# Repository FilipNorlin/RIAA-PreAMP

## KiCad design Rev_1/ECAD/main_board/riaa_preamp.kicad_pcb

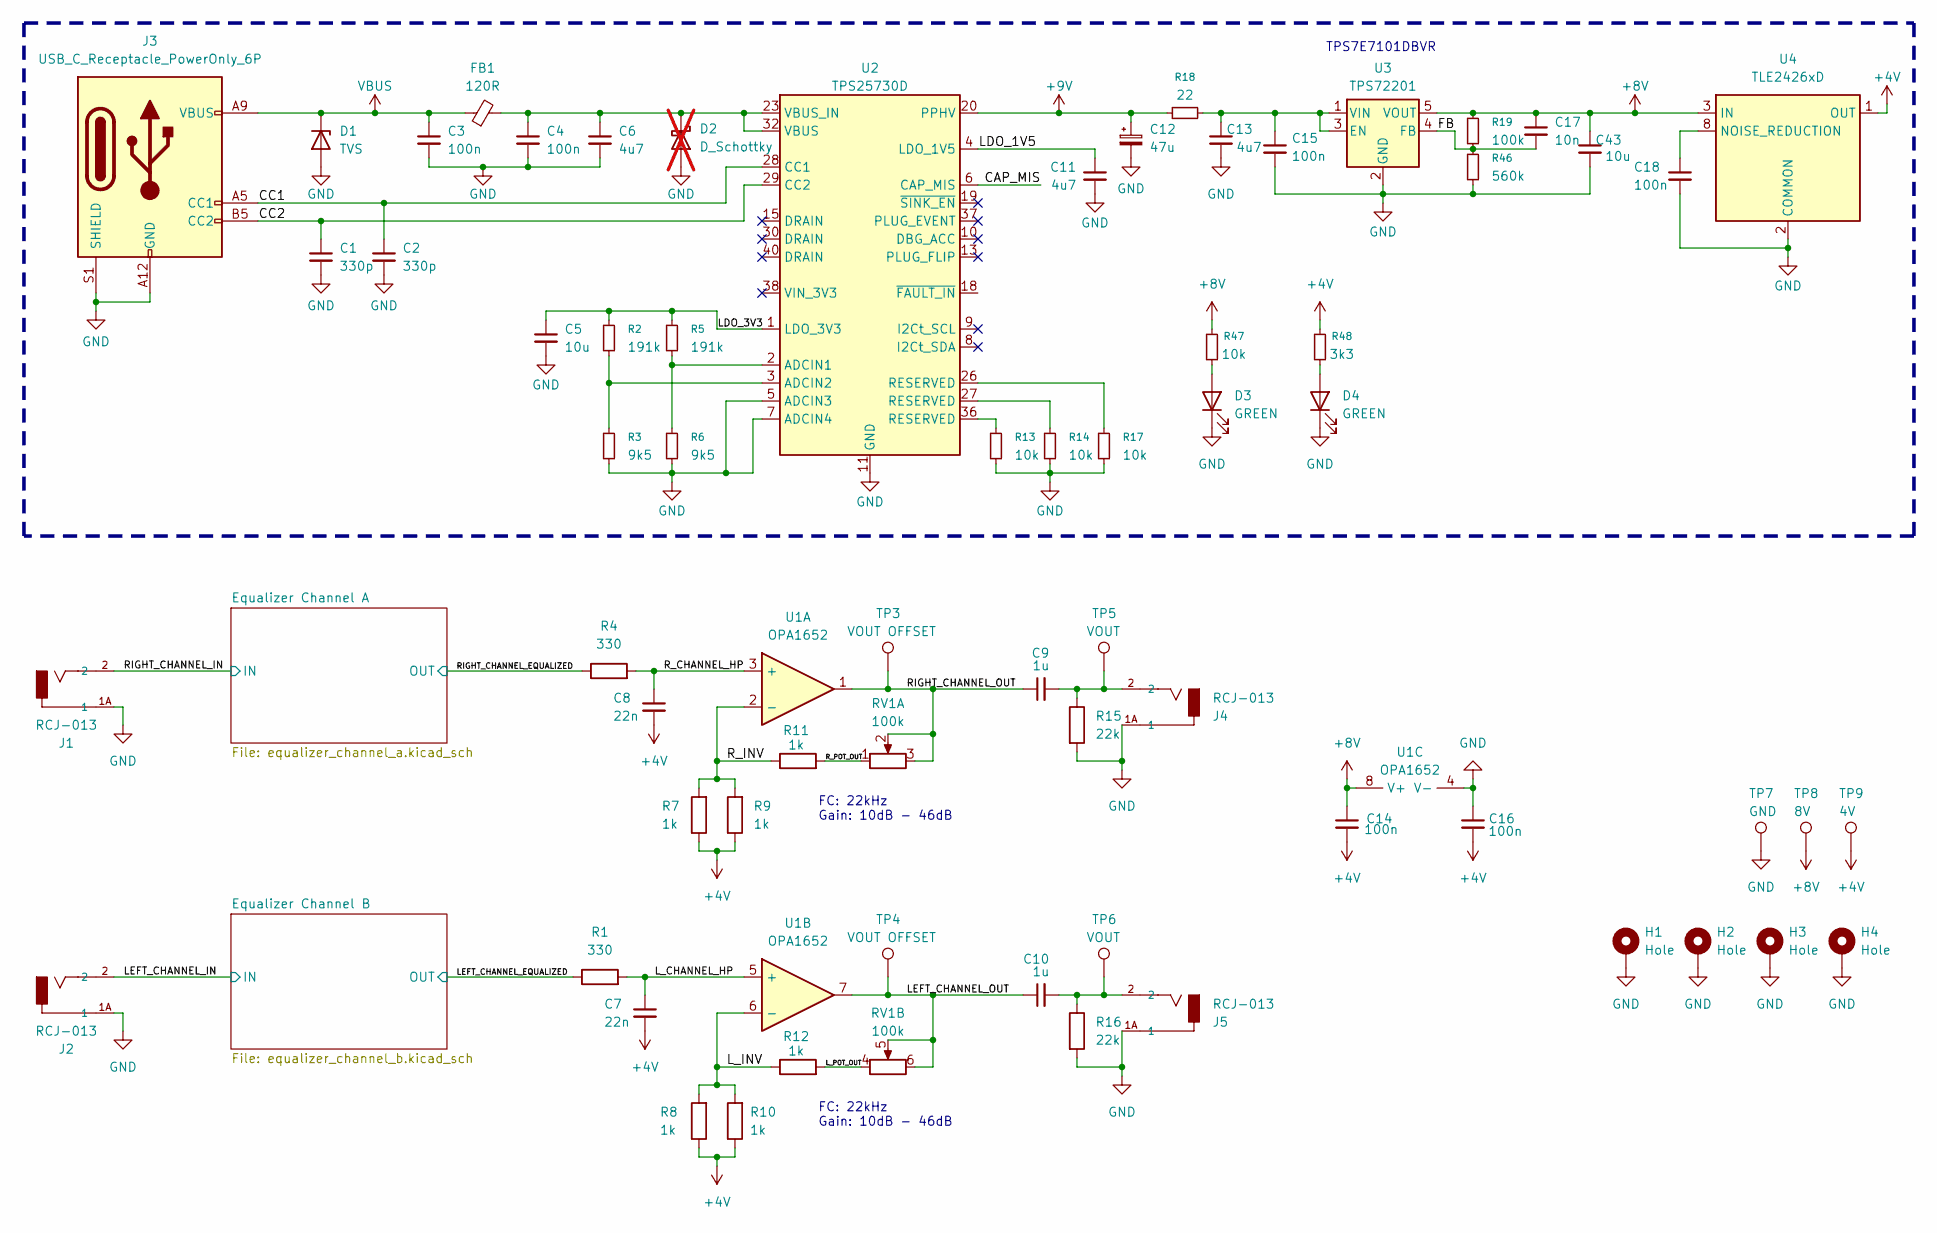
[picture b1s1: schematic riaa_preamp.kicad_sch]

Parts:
C1, C2: 330p; C_0805_2012Metric
C3, C4, C14, C15, C16, C18: 100n; C_0805_2012Metric
C5, C43: 10u; C_0805_2012Metric
C6, C11, C13: 4u7; C_0805_2012Metric
C7, C8: 22n; C_0805_2012Metric
C9, C10: 1u; C_0805_2012Metric
C12: 47u; C_Radial_D6.3mm_H11.0mm_P2.50mm
C17: 10n; C_0603_1608Metric
D1: TVS; D_SOD-123
D2: D_Schottky; D_SOD-123; not fitted
D3, D4: GREEN; LED_1206_3216Metric
FB1: 120R; L_0805_2012Metric
H1, H2, H3, H4: Hole; MountingHole_2.7mm_M2.5_ISO14580_Pad
J1, J2, J4, J5: RCJ-013; PART_REV B
J3: USB_C_Receptacle_PowerOnly_6P; USB_C_Receptacle_GCT_USB4125-xx-x-0190_6P_TopMnt_Horizontal
R1, R4: 330; R_0805_2012Metric
R2, R5: 191k; R_0603_1608Metric
R3, R6: 9k5; R_0603_1608Metric
R7, R8, R9, R10, R11, R12: 1k; R_0805_2012Metric
R13, R14, R17, R47: 10k; R_0603_1608Metric
R15, R16: 22k; R_0805_2012Metric
R18: 22; R_0603_1608Metric
R19: 100k; R_0805_2012Metric
R46: 560k; R_0603_1608Metric
R48: 3k3; R_0603_1608Metric
RV1: 100k
TP3, TP4: VOUT OFFSET; TestPoint_Pad_1.0x1.0mm
TP5, TP6: VOUT; TestPoint_Pad_1.0x1.0mm
TP7: GND; TestPoint_THTPad_1.0x1.0mm_Drill0.5mm
TP8: 8V; TestPoint_THTPad_1.0x1.0mm_Drill0.5mm
TP9: 4V; TestPoint_THTPad_1.0x1.0mm_Drill0.5mm
U1: OPA1652; JEITA_SOIC-8_3.9x4.9mm_P1.27mm
U2: TPS25730D; Texas_REF0038A_WQFN-38-2EP_6x4mm_P0.4
U3: TPS72201; SOT-23-5
U4: TLE2426xD; SOIC-8_3.9x4.9mm_P1.27mm

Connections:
+4V: C7.2, C8.2, C14.2, C16.2, R7.1, R8.1, R9.1, R10.1, R48.1, TP9.1 (1_1), U4.1 (OUT); also elsewhere on the board
+8V: C14.1, C17.1, C43.1, R19.1, R47.1, TP8.1 (1_1), U1.8 (V+), U3.5 (VOUT), U4.3 (IN); also elsewhere on the board
+9V: C12.1, R18.1, U2.20 (PPHV)
/CAP_MIS: U2.6 (CAP_MIS)
/CC1: C2.1, J3.A5 (CC1), U2.28 (CC1)
/CC2: C1.1, J3.B5 (CC2), U2.29 (CC2)
/FB: C17.2, R19.2, R46.1, U3.4 (FB)
/LDO_1V5: C11.1, U2.4 (LDO_1V5)
/LDO_3V3: C5.1, R2.1, R5.1, U2.1 (LDO_3V3)
/LEFT_CHANNEL_EQUALIZED: R1.1; also elsewhere on the board
/LEFT_CHANNEL_IN: J2.2; also elsewhere on the board
/LEFT_CHANNEL_OUT: C10.1, RV1.5, RV1.6, TP4.1 (1_1), U1.7
/L_CHANNEL_HP: C7.1, R1.2, U1.5 (+)
/L_INV: R8.2, R10.2, R12.1, U1.6 (-)
/L_POT_OUT: R12.2, RV1.4
/RIGHT_CHANNEL_EQUALIZED: R4.1; also elsewhere on the board
/RIGHT_CHANNEL_IN: J1.2; also elsewhere on the board
/RIGHT_CHANNEL_OUT: C9.1, RV1.2, RV1.3, TP3.1 (1_1), U1.1
/R_CHANNEL_HP: C8.1, R4.2, U1.3 (+)
/R_INV: R7.2, R9.2, R11.1, U1.2 (-)
/R_POT_OUT: R11.2, RV1.1
GND: C1.2, C2.2, C3.2, C4.2, C5.2, C6.2, C11.2, C12.2, C13.2, C15.2, C16.1, C18.2, C43.2, D1.2 (A), D2.2 (A), D3.1 (K), D4.1 (K), H1.1 (1_1), H2.1 (1_1), H3.1 (1_1), H4.1 (1_1), J1.1A (1), J1.1B (1), J1.1C (1), J2.1A (1), J2.1B (1), J2.1C (1), J3.A12 (GND), J3.B12 (GND), J3.S1 (SHIELD), J4.1A (1), J4.1B (1), J4.1C (1), J5.1A (1), J5.1B (1), J5.1C (1), R3.2, R6.2, R13.2, R14.2, R15.2, R16.2, R17.2, R46.2, TP7.1 (1_1), U1.4 (V-), U2.5 (ADCIN3), U2.7 (ADCIN4), U2.11 (GND), U2.12 (GND), U2.14 (GND), U2.16 (GND), U2.17 (GND), U2.31 (GND), U2.34 (GND), U2.39 (GND), U3.2 (GND), U4.2 (COMMON); also elsewhere on the board
unnamed: C9.2, J4.2, R15.1, TP5.1 (1_1)
unnamed: C10.2, J5.2, R16.1, TP6.1 (1_1)
unnamed: C4.1, C6.1, D2.1 (K), FB1.2, U2.23 (VBUS_IN), U2.32 (VBUS)
unnamed: D3.2 (A), R47.2
unnamed: D4.2 (A), R48.2
unnamed: R13.1, U2.36 (RESERVED)
unnamed: R14.1, U2.27 (RESERVED)
unnamed: R17.1, U2.26 (RESERVED)
unnamed: R5.2, R6.1, U2.2 (ADCIN1)
unnamed: R2.2, R3.1, U2.3 (ADCIN2)
unnamed: C13.1, C15.1, R18.2, U3.1 (VIN), U3.3 (EN)
unnamed: C18.1, U4.8 (NOISE_REDUCTION)
VBUS: C3.1, D1.1 (K), FB1.1, J3.A9 (VBUS), J3.B9 (VBUS)

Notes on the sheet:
TPS7E7101DBVR
FC: 22kHz Gain: 10dB - 46dB

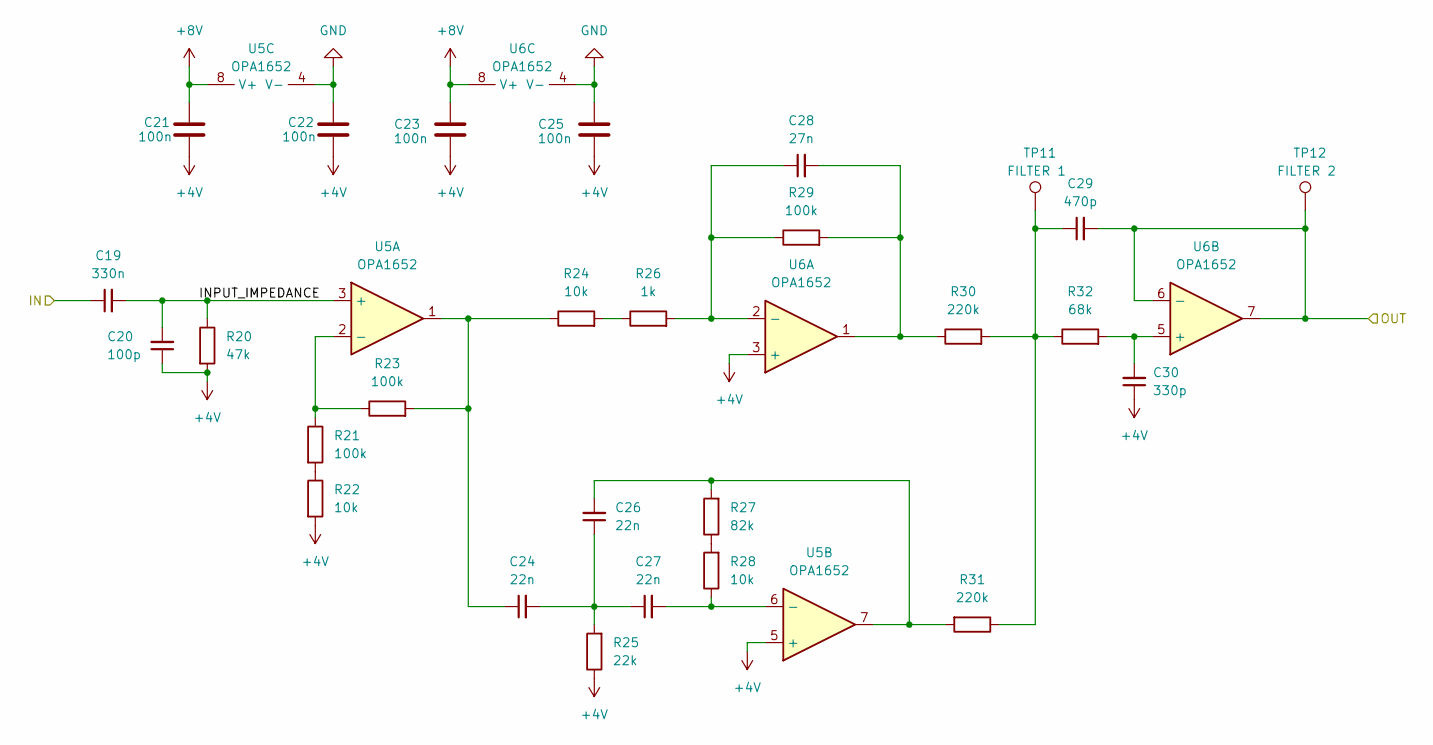
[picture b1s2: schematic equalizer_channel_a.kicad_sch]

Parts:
C19: 330n; C_0805_2012Metric
C20: 100p; C_0805_2012Metric
C21, C22, C23, C25: 100n; C_0805_2012Metric
C24, C26, C27: 22n; C_0805_2012Metric
C28: 27n; C_0805_2012Metric
C29: 470p; C_0805_2012Metric
C30: 330p; C_0805_2012Metric
R20: 47k; R_0805_2012Metric
R21, R23, R29: 100k; R_0805_2012Metric
R22, R24, R28: 10k; R_0805_2012Metric
R25: 22k; R_0805_2012Metric
R26: 1k; R_0805_2012Metric
R27: 82k; R_0805_2012Metric
R30, R31: 220k; R_0805_2012Metric
R32: 68k; R_0805_2012Metric
TP11: FILTER 1; TestPoint_Pad_1.0x1.0mm
TP12: FILTER 2; TestPoint_Pad_1.0x1.0mm
U5, U6: OPA1652; JEITA_SOIC-8_3.9x4.9mm_P1.27mm

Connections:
+4V: C20.1, C21.2, C22.2, C23.1, C25.1, C30.1, R20.2, R22.2, R25.1, U5.5 (+), U6.3 (+); also elsewhere on the board
+8V: C21.1, C23.2, U5.8 (V+), U6.8 (V+); also elsewhere on the board
/Equalizer Channel A/INPUT_IMPEDANCE: C19.2, C20.2, R20.1, U5.3 (+)
/RIGHT_CHANNEL_EQUALIZED: C29.2, TP12.1 (1_1), U6.6 (-), U6.7; also elsewhere on the board
/RIGHT_CHANNEL_IN: C19.1; also elsewhere on the board
GND: C22.1, C25.2, U5.4 (V-), U6.4 (V-); also elsewhere on the board
unnamed: C24.1, R23.2, R24.1, U5.1
unnamed: C24.2, C26.1, C27.1, R25.2
unnamed: C26.2, R27.2, R31.2, U5.7
unnamed: C28.2, R29.2, R30.1, U6.1
unnamed: C29.1, R30.2, R31.1, R32.1, TP11.1 (1_1)
unnamed: R21.2, R22.1
unnamed: R24.2, R26.1
unnamed: R27.1, R28.2
unnamed: R21.1, R23.1, U5.2 (-)
unnamed: C27.2, R28.1, U5.6 (-)
unnamed: C28.1, R26.2, R29.1, U6.2 (-)
unnamed: C30.2, R32.2, U6.5 (+)

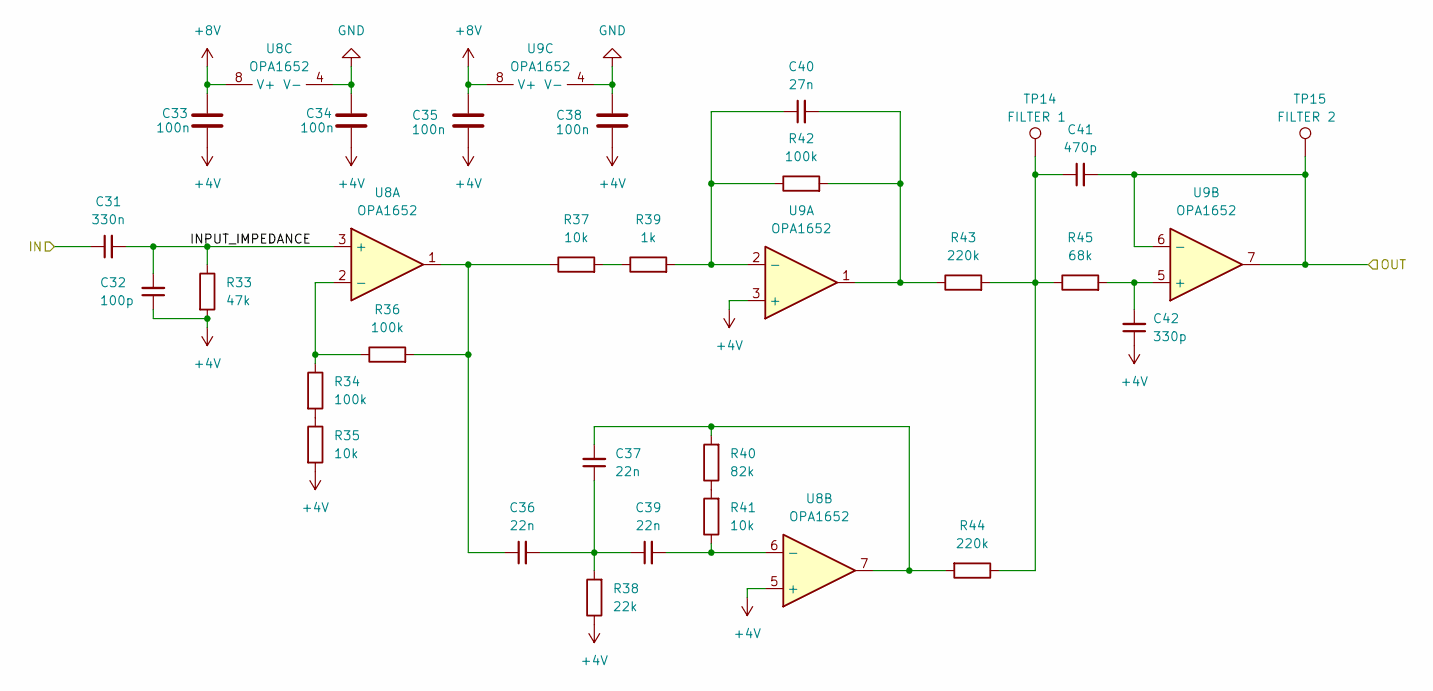
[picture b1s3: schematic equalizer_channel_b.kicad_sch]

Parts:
C31: 330n; C_0805_2012Metric
C32: 100p; C_0805_2012Metric
C33, C34, C35, C38: 100n; C_0805_2012Metric
C36, C37, C39: 22n; C_0805_2012Metric
C40: 27n; C_0805_2012Metric
C41: 470p; C_0805_2012Metric
C42: 330p; C_0805_2012Metric
R33: 47k; R_0805_2012Metric
R34, R36, R42: 100k; R_0805_2012Metric
R35, R37, R41: 10k; R_0805_2012Metric
R38: 22k; R_0805_2012Metric
R39: 1k; R_0805_2012Metric
R40: 82k; R_0805_2012Metric
R43, R44: 220k; R_0805_2012Metric
R45: 68k; R_0805_2012Metric
TP14: FILTER 1; TestPoint_Pad_1.0x1.0mm
TP15: FILTER 2; TestPoint_Pad_1.0x1.0mm
U8, U9: OPA1652; JEITA_SOIC-8_3.9x4.9mm_P1.27mm

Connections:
+4V: C32.1, C33.2, C34.2, C35.1, C38.1, C42.1, R33.2, R35.2, R38.1, U8.5 (+), U9.3 (+); also elsewhere on the board
+8V: C33.1, C35.2, U8.8 (V+), U9.8 (V+); also elsewhere on the board
/Equalizer Channel B/INPUT_IMPEDANCE: C31.2, C32.2, R33.1, U8.3 (+)
/LEFT_CHANNEL_EQUALIZED: C41.2, TP15.1 (1_1), U9.6 (-), U9.7; also elsewhere on the board
/LEFT_CHANNEL_IN: C31.1; also elsewhere on the board
GND: C34.1, C38.2, U8.4 (V-), U9.4 (V-); also elsewhere on the board
unnamed: C36.1, R36.2, R37.1, U8.1
unnamed: C36.2, C37.1, C39.1, R38.2
unnamed: C37.2, R40.2, R44.2, U8.7
unnamed: C40.2, R42.2, R43.1, U9.1
unnamed: C41.1, R43.2, R44.1, R45.1, TP14.1 (1_1)
unnamed: R34.2, R35.1
unnamed: R37.2, R39.1
unnamed: R40.1, R41.2
unnamed: R34.1, R36.1, U8.2 (-)
unnamed: C39.2, R41.1, U8.6 (-)
unnamed: C40.1, R39.2, R42.1, U9.2 (-)
unnamed: C42.2, R45.2, U9.5 (+)

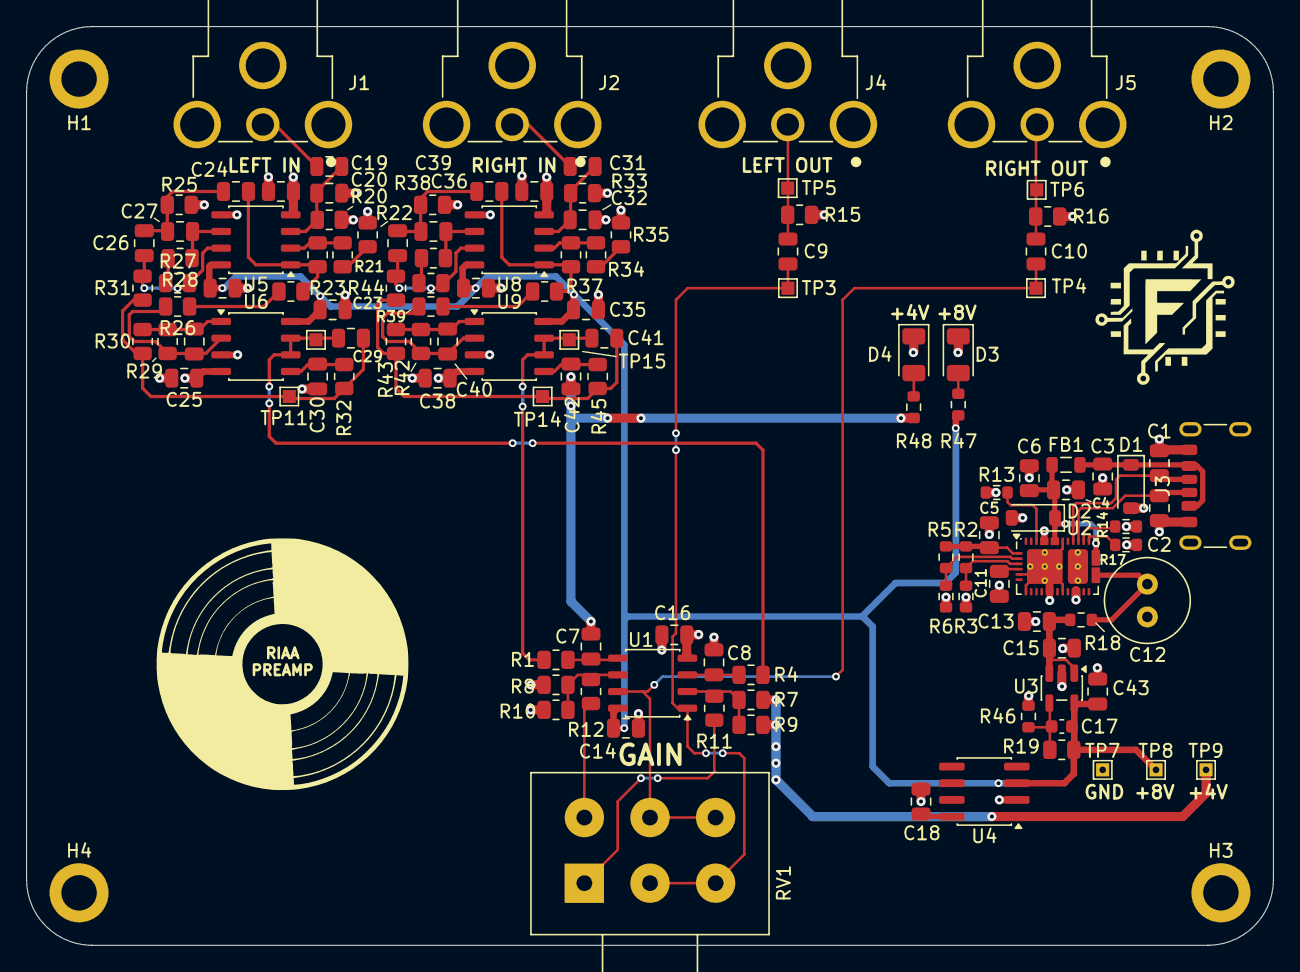
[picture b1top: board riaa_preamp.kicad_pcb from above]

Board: 4 copper layers, 95.0 x 70.0 mm, 125 parts (0 on the bottom side), 60 nets.

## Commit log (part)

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2026-04-21 Updated gitignore
2026-04-21 First rough schematic
2026-04-21 RIAA Simulation
2026-04-26 Semi finsihed schematic
2026-06-27 Finished
